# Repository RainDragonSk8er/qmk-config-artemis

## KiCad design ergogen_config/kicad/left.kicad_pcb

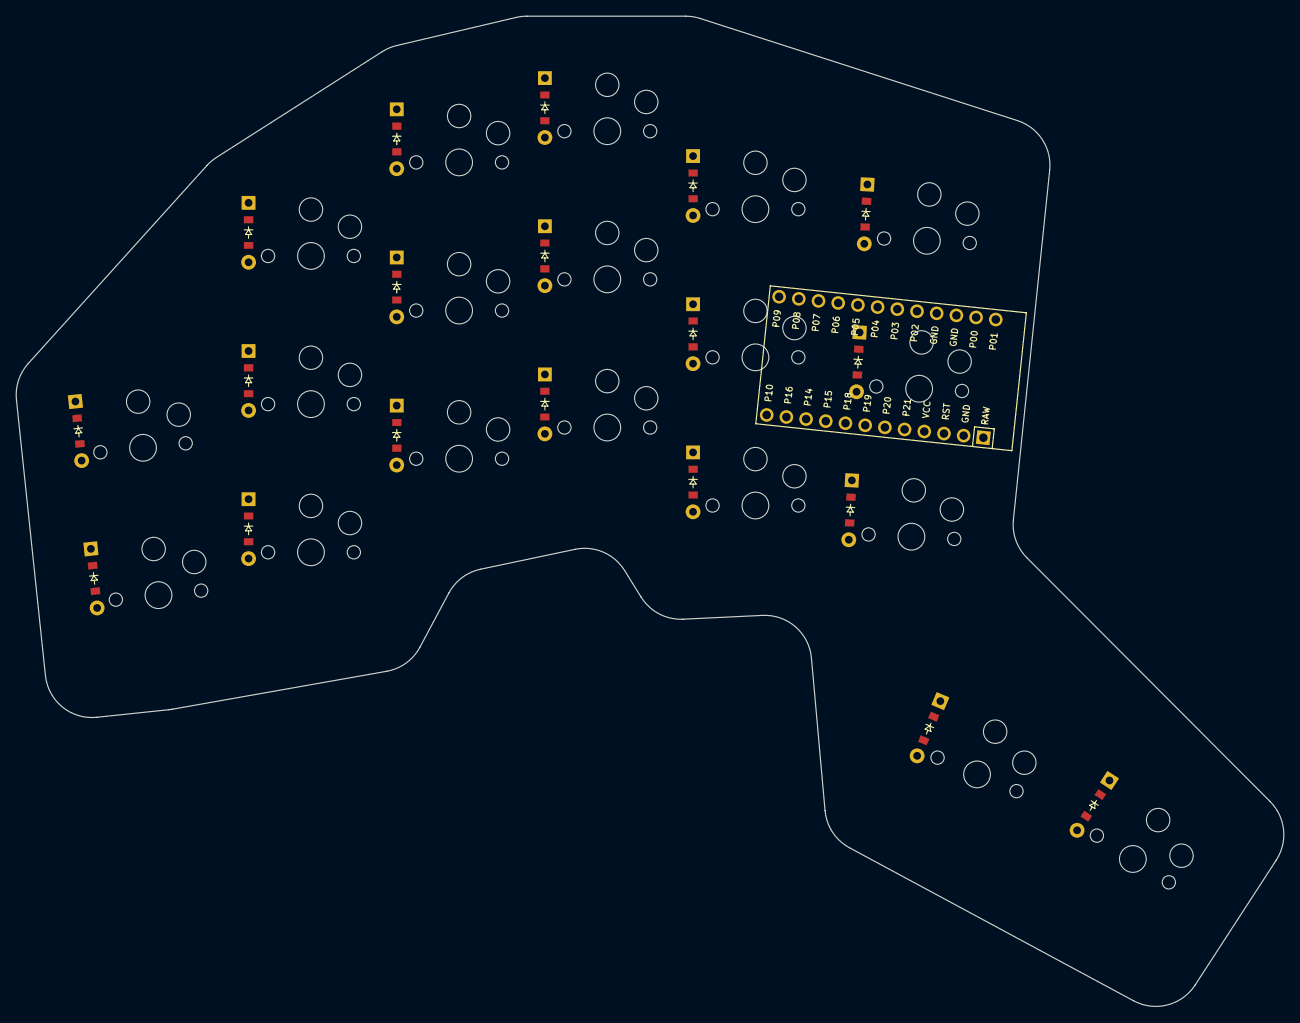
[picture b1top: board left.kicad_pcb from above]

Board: 2 copper layers, 162.6 x 127.0 mm, 39 parts (0 on the bottom side), 31 nets, no tracks yet.

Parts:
D1, D2, D3, D4, D5, D6, D7, D8, D9, D10, D11, D12, D13, D14, D15, D16, D17, D18, D19: ComboDiode
MCU1: ProMicro
S1, S2, S3, S4, S5, S6, S7, S8, S9, S10, S11, S12, S13, S14, S15, S16, S17, S18, S19: PG1350

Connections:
GND: MCU1.2, MCU1.15, MCU1.16
P3: MCU1.18, S1.1, S2.1
P4: MCU1.19, S3.1, S4.1, S5.1
P5: MCU1.20, S6.1, S7.1, S8.1
P6: MCU1.21, S9.1, S10.1, S11.1
P7: MCU1.22, S12.1, S13.1, S14.1
P8: MCU1.23, S15.1, S16.1, S17.1, S18.1
P9: MCU1.24, S19.1
P10: D18.1, D19.1, MCU1.12
P14: D2.1, D4.1, D7.1, D10.1, D13.1, D16.1, MCU1.10
P15: D1.1, D3.1, D6.1, D9.1, D12.1, D15.1, MCU1.9
P16: D5.1, D8.1, D11.1, D14.1, D17.1, MCU1.11
home_thumb: D19.2, S19.2
index_bottom: D12.2, S12.2
index_home: D13.2, S13.2
index_top: D14.2, S14.2
inner_bottom: D15.2, S15.2
inner_home: D16.2, S16.2
inner_top: D17.2, S17.2
middle_bottom: D9.2, S9.2
middle_home: D10.2, S10.2
middle_top: D11.2, S11.2
near_thumb: D18.2, S18.2
outer_bottom: D1.2, S1.2
outer_home: D2.2, S2.2
pinky_bottom: D3.2, S3.2
pinky_home: D4.2, S4.2
pinky_top: D5.2, S5.2
ring_bottom: D6.2, S6.2
ring_home: D7.2, S7.2
ring_top: D8.2, S8.2

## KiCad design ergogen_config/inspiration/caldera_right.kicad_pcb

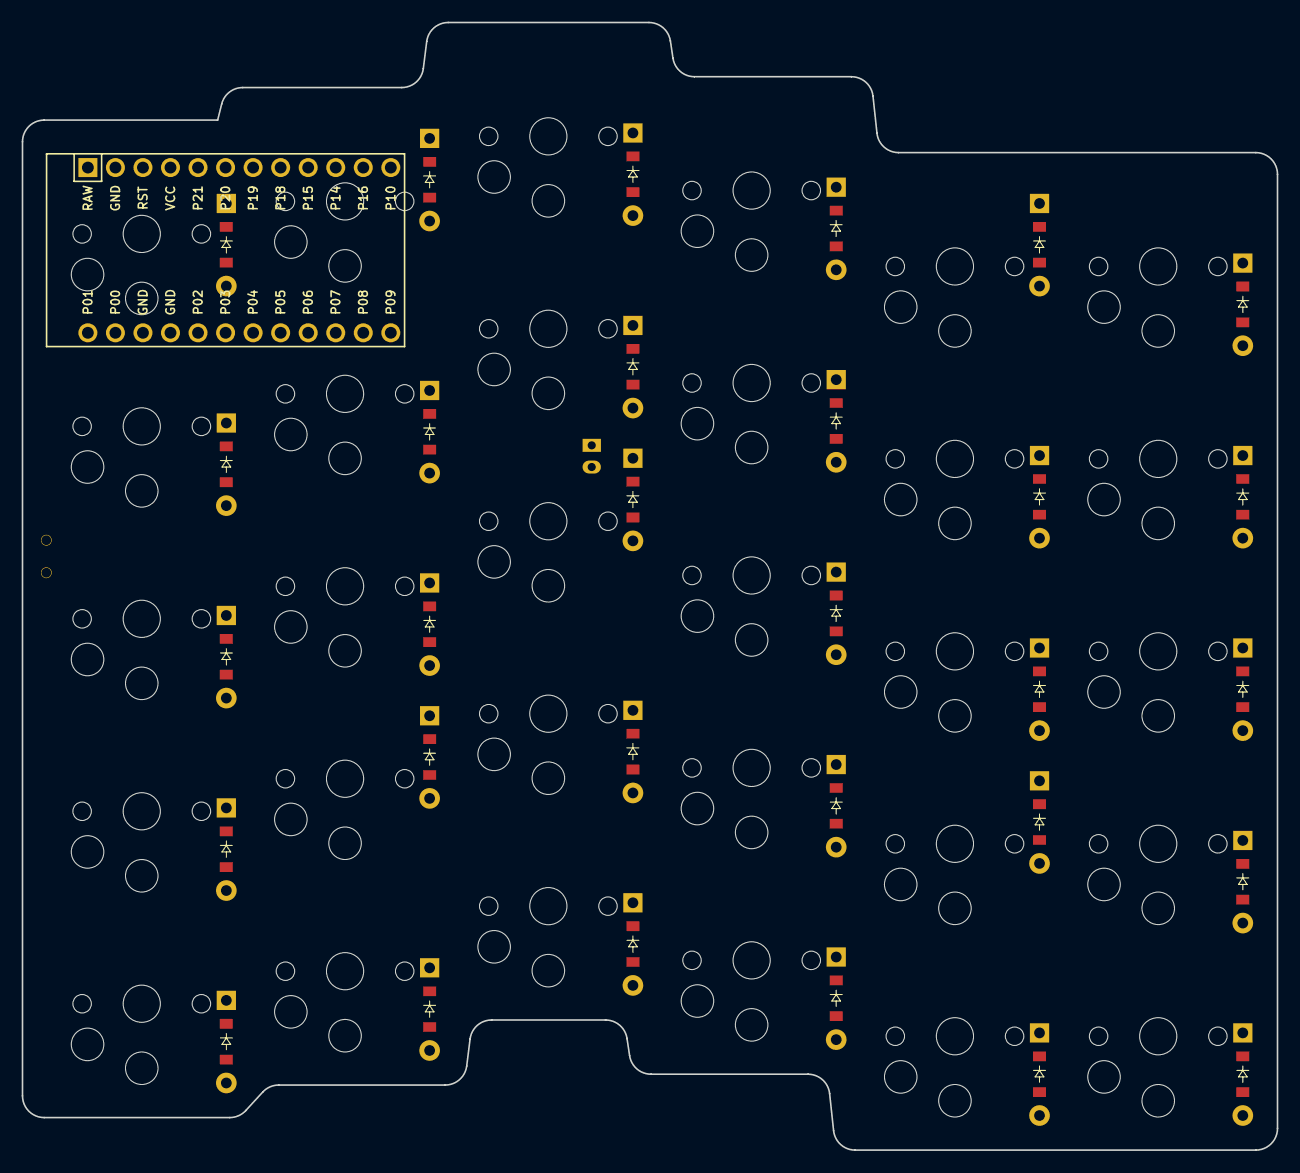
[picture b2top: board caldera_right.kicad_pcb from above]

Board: 2 copper layers, 115.8 x 104.0 mm, 63 parts (0 on the bottom side), 44 nets, no tracks yet.

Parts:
D1, D2, D3, D4, D5, D6, D7, D8, D9, D10, D11, D12, D13, D14, D15, D16, D17, D18, D19, D20, D21, D22, D23, D24, D25, D26, D27, D28, D29, D30: ComboDiode
JST1: JST_PH_S2B-PH-K_02x2.00mm_Angled
MCU1: ProMicro
S1, S2, S3, S4, S5, S6, S7, S8, S9, S10, S11, S12, S13, S14, S15, S16, S17, S18, S19, S20, S21, S22, S23, S24, S25, S26, S27, S28, S29, S30: PG1350
T1: SPDT_C128955

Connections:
GND: JST1.2, MCU1.2, MCU1.15, MCU1.16
P002: D3.1, D7.1, D11.1, D19.1, D23.1, D27.1
P011: S21.1, S22.1, S23.1, S24.1, S25.1
P017: S26.1, S27.1, S28.1, S29.1, S30.1
P020: S1.1, S2.1, S3.1, S4.1, S5.1
P022: S6.1, S7.1, S8.1, S9.1, S10.1
P024: S11.1, S12.1, S13.1, S14.1, S15.1
P029: D4.1, D8.1, D12.1, D16.1, D20.1, D24.1
P031: D5.1, D13.1, D17.1, D26.1, D29.1, D30.1
P100: S16.1, S17.1, S18.1, S19.1, S20.1
P113: D1.1, D6.1, D9.1, D14.1, D18.1, D21.1
P115: D2.1, D10.1, D15.1, D22.1, D25.1, D28.1
RAW: MCU1.1, T1.2
mirror_fifth_bottom: D28.2, S22.2
mirror_fifth_home: D19.2, S23.2
mirror_fifth_mod: D18.2, S21.2
mirror_fifth_num: D29.2, S25.2
mirror_fifth_top: D20.2, S24.2
mirror_first_bottom: D2.2, S2.2
mirror_first_home: D3.2, S3.2
mirror_first_mod: D1.2, S1.2
mirror_first_num: D5.2, S5.2
mirror_first_top: D4.2, S4.2
mirror_fourth_bottom: D15.2, S17.2
mirror_fourth_home: D27.2, S18.2
mirror_fourth_mod: D14.2, S16.2
mirror_fourth_num: D17.2, S20.2
mirror_fourth_top: D16.2, S19.2
mirror_second_bottom: D25.2, S7.2
mirror_second_home: D7.2, S8.2
mirror_second_mod: D6.2, S6.2
mirror_second_num: D26.2, S10.2
mirror_second_top: D8.2, S9.2
mirror_sixth_bottom: D22.2, S27.2
mirror_sixth_home: D23.2, S28.2
mirror_sixth_mod: D21.2, S26.2
mirror_sixth_num: D30.2, S30.2
mirror_sixth_top: D24.2, S29.2
mirror_third_bottom: D10.2, S12.2
mirror_third_home: D11.2, S13.2
mirror_third_mod: D9.2, S11.2
mirror_third_num: D13.2, S15.2
mirror_third_top: D12.2, S14.2
pos: JST1.1, T1.1

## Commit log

2024-09-20 Initial commit of Artemis Ergogen yaml config
